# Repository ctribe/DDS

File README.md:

# DDS
100MHz DDS Signal Source

This signal source is based on the AD9913 DDS Chip and will interface to a STM32F4 Microcontroller. Output power and frequency are set using a rotary encoder with a push button. 

Design Goals:

Pout Max: +20dBm

Dynamic Range: 50dB

SFDR: 70dBc

Frequency Range: 10kHz - 100MHz

User Interface:
LCD & Rotary Encoder

Features:

1dB incremental adjustments

Variable frequency step size

Coax output

More info coming soon.

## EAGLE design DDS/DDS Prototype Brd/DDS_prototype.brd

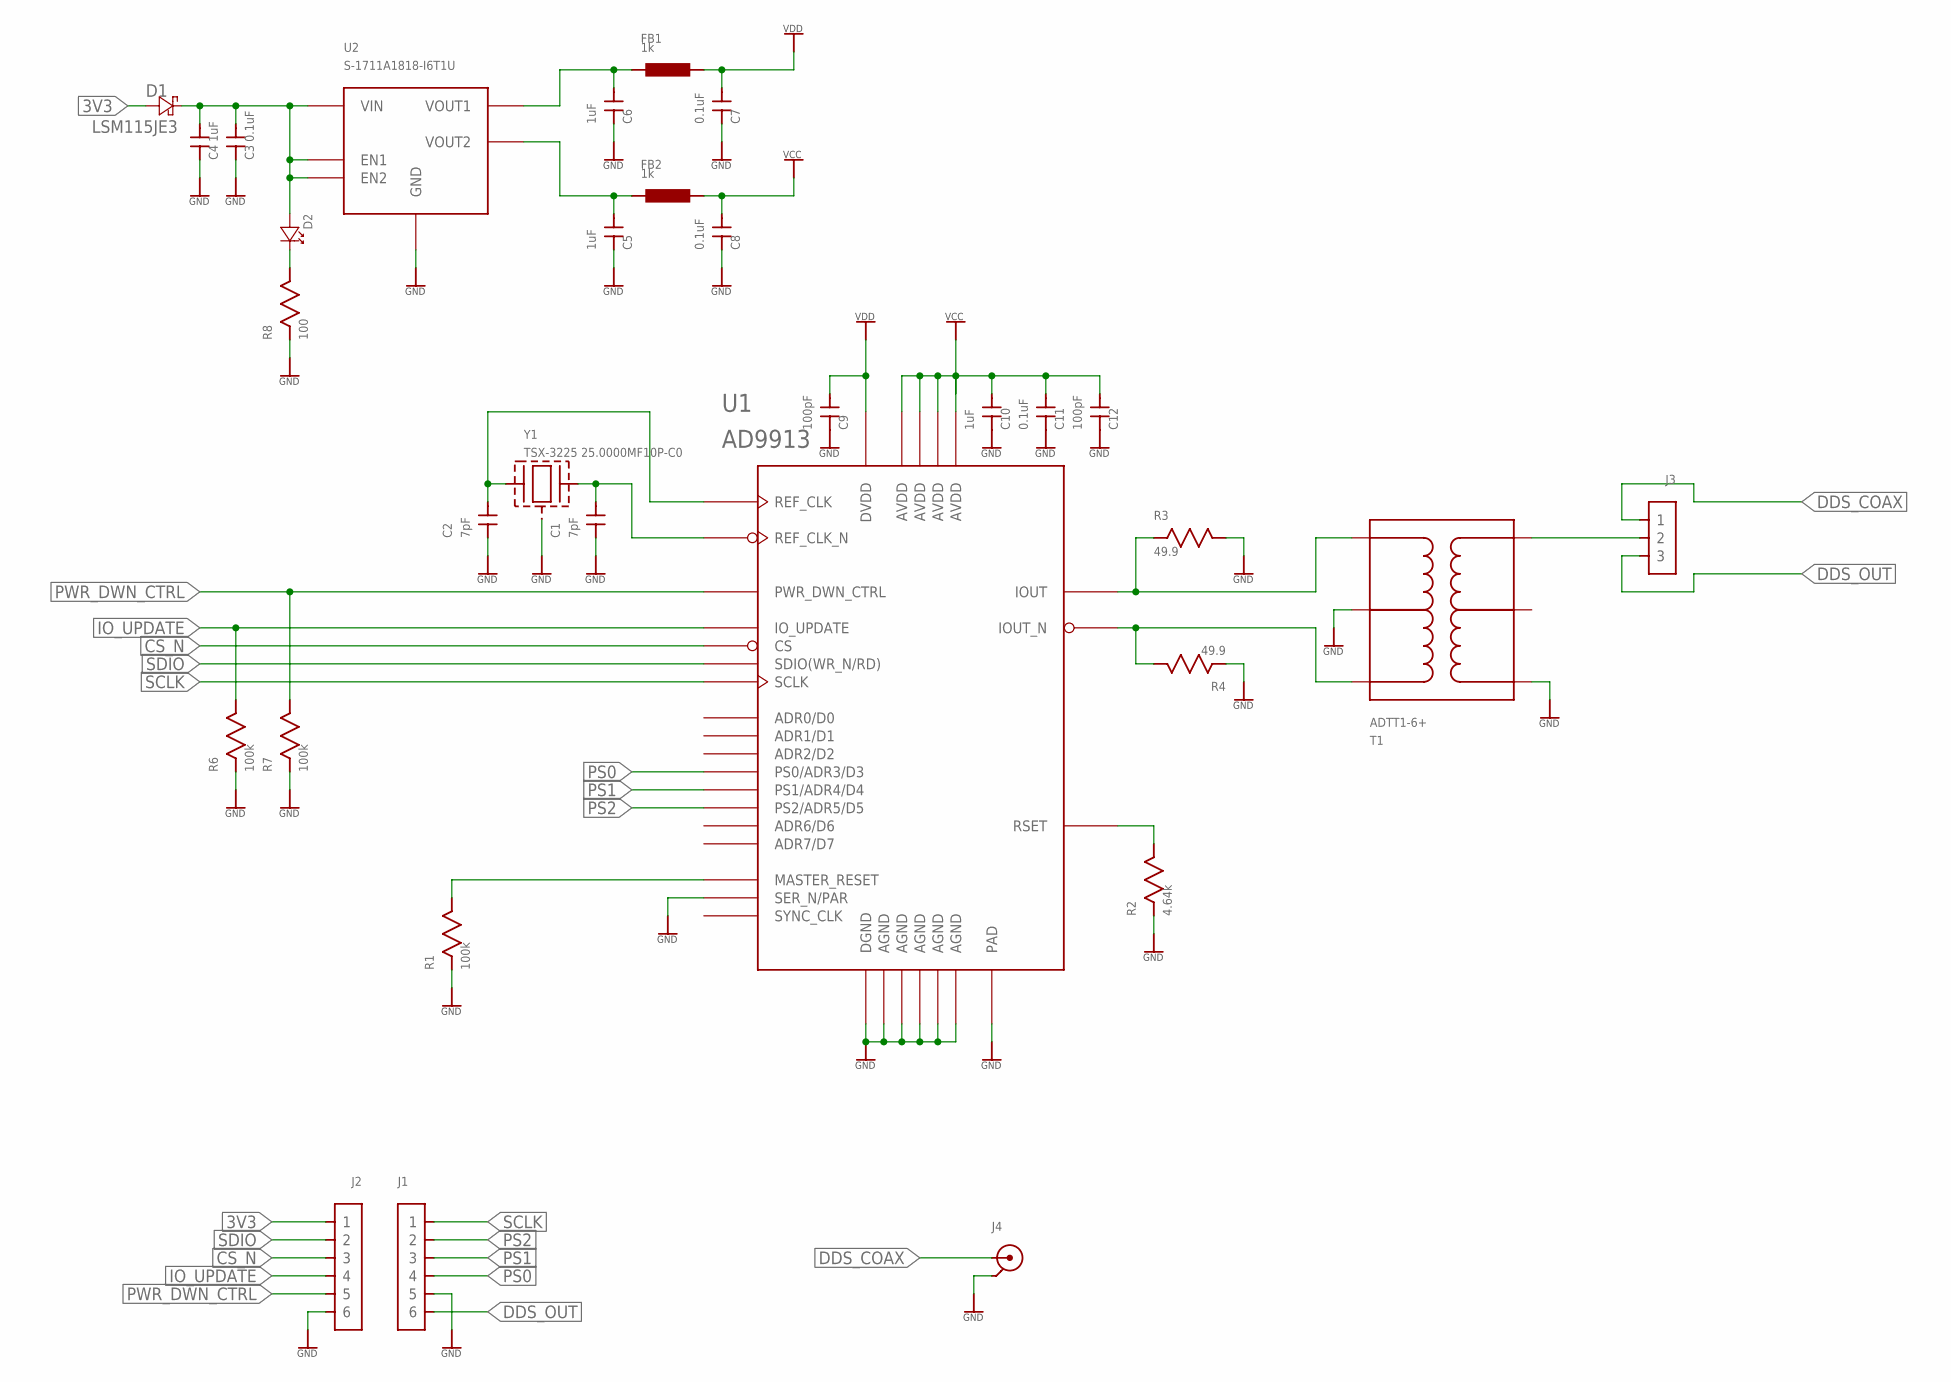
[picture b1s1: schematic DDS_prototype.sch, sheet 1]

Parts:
C1, C2: 7pF; 0402
C3, C7, C8, C11: 0.1uF; 0402
C4, C5, C6, C10: 1uF; 0402
C9, C12: 100pF; 0402
D1: LSM115JE3; DO-214BA
D2: QBLP595-IG; 0402_GREEN
FB1, FB2: 1k; 0603
J1, J2: 1X6_MALE_HEADER_0.1
J3: 1X3_MALE_HEADER_0.1
J4: SMA_EMPCB.SMAFSTJ.B.HT; EMPCB.SMAFSTJ.B.HT
R1, R6, R7: 100k; 0402
R2: 4.64k; 0402
R3, R4: 49.9; 0402
R8: 100; 0402
T1: ADTT1-6+; CD637
U1: AD9913; 32-LFCSP
U2: S-1711A1818-I6T1U; SNT-6A
Y1: TSX-3225 25.0000MF10P-C0; TSX-3225

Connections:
3V3: D1.A, J2.P$1 (1)
3V3_PROT: C3.2, C4.2, D1.K, D2.A, U2.P2 (VIN), U2.P4 (EN2), U2.P6 (EN1)
CS_N: J2.P$3 (3), U1.P$28 (CS)
DDS: J3.P$2 (2), T1.P$4
DDS_COAX: J3.P$1 (1), J4.P$1
DDS_OUT: J1.P$6 (6), J3.P$3 (3)
GND: C1.1, C2.1, C3.1, C4.1, C5.1, C6.1, C7.1, C8.1, C9.1, C10.1, C11.1, C12.1, J1.P$5 (5), J2.P$6 (6), J4.P$2, J4.P$3, J4.P$4, J4.P$5, R1.P$1, R2.P$1, R3.P$2, R4.P$1, R6.P$1, R7.P$1, R8.P$1, T1.P$2, T1.P$6, U1.P$5 (DGND), U1.P$10 (SER_N/PAR), U1.P$11 (AGND), U1.P$15 (AGND), U1.P$18 (AGND), U1.P$21 (AGND), U1.P$23 (AGND), U1.P$33 (PAD), U2.P5 (GND), Y1.P2, Y1.P4
IOUT: R3.P$1, T1.P$3, U1.P$19 (IOUT)
IOUT_N: R4.P$2, T1.P$1, U1.P$20 (IOUT_N)
IO_UPDATE: J2.P$4 (4), R6.P$2, U1.P$27 (IO_UPDATE)
MSTR_RST: R1.P$2, U1.P$25 (MASTER_RESET)
unnamed: D2.K, R8.P$2
unnamed: C1.2, U1.P$14 (REF_CLK_N), Y1.P3
unnamed: C2.2, U1.P$13 (REF_CLK), Y1.P1
PS0: J1.P$4 (4), U1.P$3 (PS0/ADR3/D3)
PS1: J1.P$3 (3), U1.P$2 (PS1/ADR4/D4)
PS2: J1.P$2 (2), U1.P$1 (PS2/ADR5/D5)
PWR_DWN_CTRL: J2.P$5 (5), R7.P$2, U1.P$26 (PWR_DWN_CTRL)
RSET: R2.P$2, U1.P$24 (RSET)
SCLK: J1.P$1 (1), U1.P$30 (SCLK)
SDIO: J2.P$2 (2), U1.P$29 (SDIO(WR_N/RD))
VCC: C8.2, C10.2, C11.2, C12.2, FB2.P$2, U1.P$12 (AVDD), U1.P$16 (AVDD), U1.P$17 (AVDD), U1.P$22 (AVDD)
VCC_UNFILT: C6.2, FB1.P$1, U2.P1 (VOUT1)
VDD: C7.2, C9.2, FB1.P$2, U1.P$4 (DVDD)
VDD_UNFILT: C5.2, FB2.P$1, U2.P3 (VOUT2)

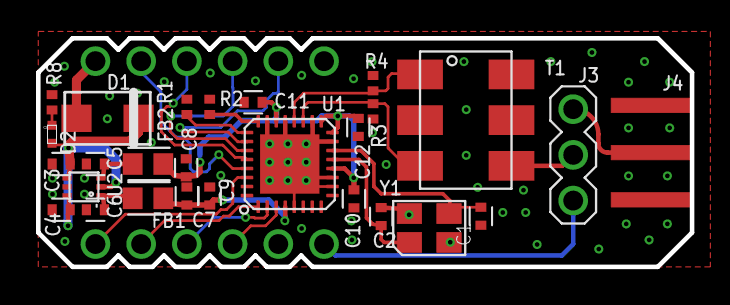
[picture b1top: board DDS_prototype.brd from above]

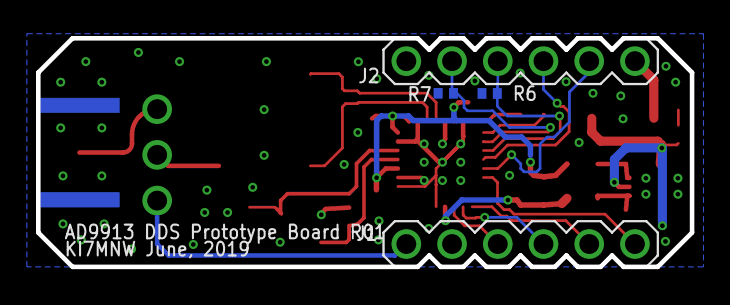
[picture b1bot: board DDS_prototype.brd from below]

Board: 2 copper layers, 36.3 x 12.7 mm, 31 parts (4 on the bottom side), 25 nets.

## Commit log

2019-06-25 Initial Commit of existing documents
2019-06-25 added pull up/down res to ctrl lines
2019-06-26 routing for pull up and pull down. not done yet.
2019-06-26 final edits to prototype board. added bom.
    final edits to prototype board. added bom. made 3d packages.
2019-06-27 updated board, now has all 3d models, libraried are now managed libs only
2019-06-28 made local copy of libraries, organized dir
2019-06-28 small readme update
2019-06-28 added gitignore
    added gitignore
2019-07-10 removed extra copy of HW libs
